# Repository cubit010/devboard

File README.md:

# Devboard
a devboard i hacked together with minimal sleep

total jlcpcb cost $28.7 (including local taxes and shipping)

5pcs pcb and 2pcs pcba

# BOM is the Devboard.csv file

# Summary:
Raspberry rp2040 microcontroller 
gpio 0-25 broken out, gpio26-29/adc0-3 also broken out 

similar pinout as raspberry pi pico, but with the gpio 25 broken out, trading a ground pin for a gpio

power pins moved to the top right of the board in a group, both vbus and 3v3

# Screenshots
## checkout (excluding tax)

## checkout (with tax)

## PCB Final

## PCB Routing

## PCB schematic

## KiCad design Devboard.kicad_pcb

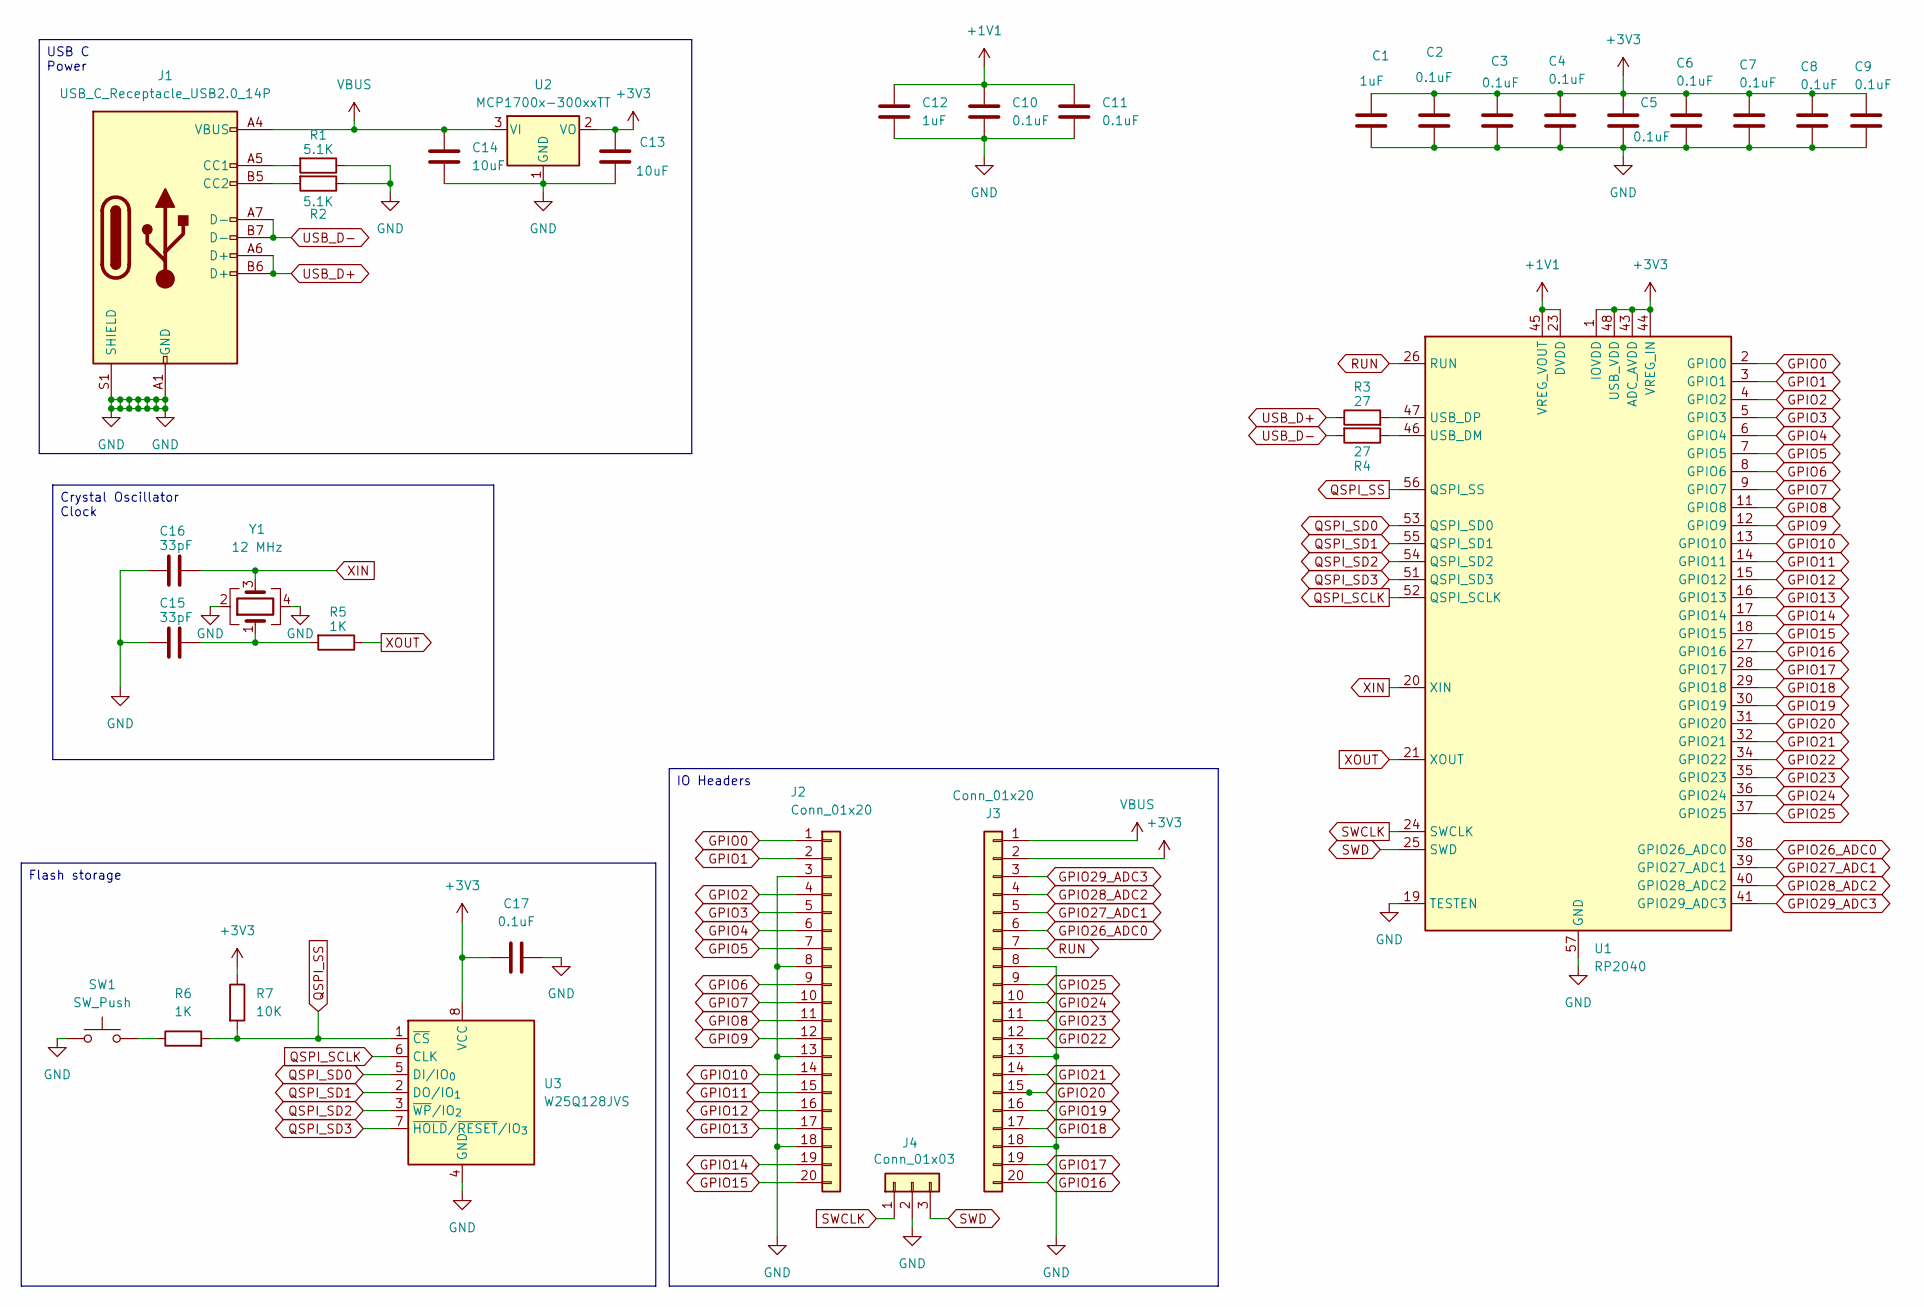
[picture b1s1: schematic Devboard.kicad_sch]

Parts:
C1, C12: 1uF; C_0402_1005Metric
C2, C3, C4, C5, C6, C7, C8, C9, C10, C11, C17: 0.1uF; C_0402_1005Metric
C13, C14: 10uF; C_0603_1608Metric
C15, C16: 33pF; C_0402_1005Metric
J1: USB_C_Receptacle_USB2.0_14P; USB_C_Receptacle_HRO_TYPE-C-31-M-12
J2, J3: Conn_01x20; PinHeader_1x20_P2.54mm_Vertical
J4: Conn_01x03; PinHeader_1x03_P2.54mm_Vertical
R1, R2: 5.1K; R_0402_1005Metric
R3, R4: 27; R_0402_1005Metric
R5, R6: 1K; R_0402_1005Metric
R7: 10K; R_0402_1005Metric
SW1: SW_Push; SW_Push_SPST_NO_Alps_SKRK
U1: RP2040; QFN-56-1EP_7x7mm_P0.4mm_EP3.2x3.2mm
U2: MCP1700x-300xxTT; SOT-23
U3: W25Q128JVS; Winbond_USON-8-1EP_3x2mm_P0.5mm_EP0.2x1.6mm
Y1: 12 MHz; Crystal_SMD_3225-4Pin_3.2x2.5mm

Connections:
+1V1: C10.1, C11.1, C12.1, U1.23 (DVDD), U1.45 (VREG_VOUT), U1.50 (DVDD)
+3V3: C1.1, C2.1, C3.1, C4.1, C5.1, C6.1, C7.1, C8.1, C9.1, C13.1, C17.1, J3.2, R7.1, U1.1 (IOVDD), U1.10 (IOVDD), U1.22 (IOVDD), U1.33 (IOVDD), U1.42 (IOVDD), U1.43 (ADC_AVDD), U1.44 (VREG_IN), U1.48 (USB_VDD), U1.49 (IOVDD), U2.2 (VO), U3.8 (VCC)
GND: C1.2, C2.2, C3.2, C4.2, C5.2, C6.2, C7.2, C8.2, C9.2, C10.2, C11.2, C12.2, C13.2, C14.2, C15.1, C16.1, C17.2, J1.A1 (GND), J1.A12 (GND), J1.B1 (GND), J1.B12 (GND), J1.S1 (SHIELD), J2.3, J2.8, J2.13, J2.18, J3.8, J3.13, J3.18, J4.2, R1.1, R2.1, SW1.1, U1.19 (TESTEN), U1.57 (GND), U2.1 (GND), U3.4 (GND), Y1.2, Y1.4
GPIO0: J2.1, U1.2 (GPIO0)
GPIO1: J2.2, U1.3 (GPIO1)
GPIO2: J2.4, U1.4 (GPIO2)
GPIO3: J2.5, U1.5 (GPIO3)
GPIO4: J2.6, U1.6 (GPIO4)
GPIO5: J2.7, U1.7 (GPIO5)
GPIO6: J2.9, U1.8 (GPIO6)
GPIO7: J2.10, U1.9 (GPIO7)
GPIO8: J2.11, U1.11 (GPIO8)
GPIO9: J2.12, U1.12 (GPIO9)
GPIO10: J2.14, U1.13 (GPIO10)
GPIO11: J2.15, U1.14 (GPIO11)
GPIO12: J2.16, U1.15 (GPIO12)
GPIO13: J2.17, U1.16 (GPIO13)
GPIO14: J2.19, U1.17 (GPIO14)
GPIO15: J2.20, U1.18 (GPIO15)
GPIO16: J3.20, U1.27 (GPIO16)
GPIO17: J3.19, U1.28 (GPIO17)
GPIO18: J3.17, U1.29 (GPIO18)
GPIO19: J3.16, U1.30 (GPIO19)
GPIO20: J3.15, U1.31 (GPIO20)
GPIO21: J3.14, U1.32 (GPIO21)
GPIO22: J3.12, U1.34 (GPIO22)
GPIO23: J3.11, U1.35 (GPIO23)
GPIO24: J3.10, U1.36 (GPIO24)
GPIO25: J3.9, U1.37 (GPIO25)
GPIO26_ADC0: J3.6, U1.38 (GPIO26_ADC0)
GPIO27_ADC1: J3.5, U1.39 (GPIO27_ADC1)
GPIO28_ADC2: J3.4, U1.40 (GPIO28_ADC2)
GPIO29_ADC3: J3.3, U1.41 (GPIO29_ADC3)
unnamed: C15.2, R5.2, Y1.1
unnamed: J1.A5 (CC1), R1.2
unnamed: J1.B5 (CC2), R2.2
unnamed: R6.1, SW1.2
unnamed: R4.1, U1.46 (USB_DM)
unnamed: R3.2, U1.47 (USB_DP)
QSPI_SCLK: U1.52 (QSPI_SCLK), U3.6 (CLK)
QSPI_SD0: U1.53 (QSPI_SD0), U3.5 (DI/IO_{0})
QSPI_SD1: U1.55 (QSPI_SD1), U3.2 (DO/IO_{1})
QSPI_SD2: U1.54 (QSPI_SD2), U3.3 (~WP/IO_{2})
QSPI_SD3: U1.51 (QSPI_SD3), U3.7 (~HOLD/~RESET/IO_{3})
QSPI_SS: R6.2, R7.2, U1.56 (QSPI_SS), U3.1 (~CS)
RUN: J3.7, U1.26 (RUN)
SWCLK: J4.1, U1.24 (SWCLK)
SWD: J4.3, U1.25 (SWD)
USB_D+: J1.A6 (D+), J1.B6 (D+), R3.1
USB_D-: J1.A7 (D-), J1.B7 (D-), R4.2
VBUS: C14.1, J1.A4 (VBUS), J1.A9 (VBUS), J1.B4 (VBUS), J1.B9 (VBUS), J3.1, U2.3 (VI)
XIN: C16.2, U1.20 (XIN), Y1.3
XOUT: R5.1, U1.21 (XOUT)

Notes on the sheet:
USB C Power
Crystal Oscillator Clock
IO Headers
Flash storage

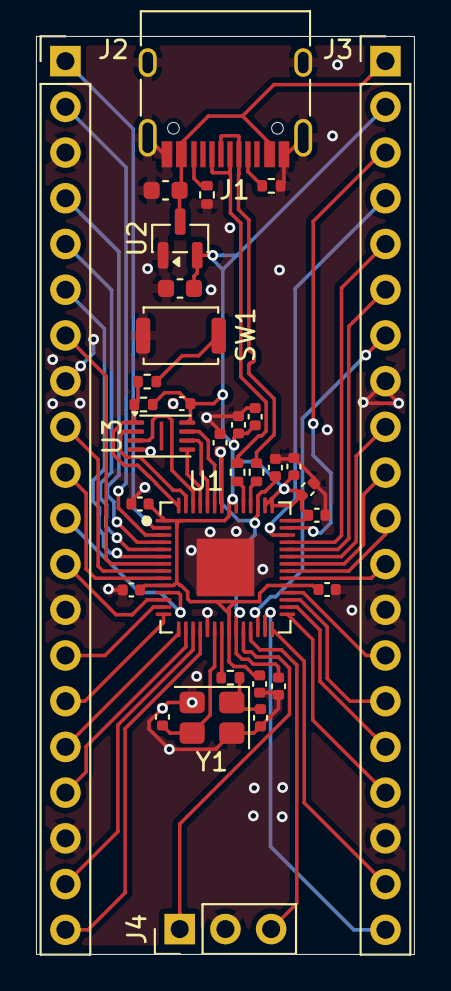
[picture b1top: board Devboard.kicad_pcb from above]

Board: 2 copper layers, 21.0 x 51.0 mm, 33 parts (0 on the bottom side), 53 nets.

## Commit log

2025-12-05 pcb files
2025-12-06 upload bom
    boom boom bom pow
2025-12-06 Revise README with project name and summary
    Updated project name and added summary details.
2025-12-06 Update README
    Clarified the power pin arrangement in the summary.
2025-12-06 Add PCB images to README
    Added images for PCB final, routing, and schematic.
2025-12-06 add production files
2025-12-06 Add cost details to README
2025-12-06 update formatting
2025-12-08 Update total cost and add checkout screenshots
    Updated the total cost in the README and added checkout screenshots.
2025-12-08 fix format
